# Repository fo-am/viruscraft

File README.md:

# Viruscraft

In this project we ask - what determines the ability of a virus to infect some hosts but not others? Working with evolutionary biologist Ben Longdon, we're developing a citizen science project using visual programming, craft, tangible interfaces and games to explore virus host shifts – where a virus jumps from one host species to another.

https://fo.am/viruscraft/

# todo

- add host extinct/virus extinct to score record
- add virus description to score record
- increase death rate with susceptibility? highly specialised = quicker extinction

aims

-

# Parameters 

These are ones that can be tweaked & need to be checked:

## host-susceptibility

Currently a probability curve between 0 (totally immune) and 1 (certain to get infection)

"returns the susceptibility of the host of infection to the supplied virus
susceptibility will range from 0..1 with 0 being completely immune
pow give us a slope so that 1 is always 1 but we reduce the likelyhood
with fewer receptors - not science"

The point here is to make the successful strategy one of continual
mutation.  In order for this to work, we need to construct a tradeoff
so that viruses with one or two of each type of ligands are not very
good. Specialist viruses should generally be successful to infect.

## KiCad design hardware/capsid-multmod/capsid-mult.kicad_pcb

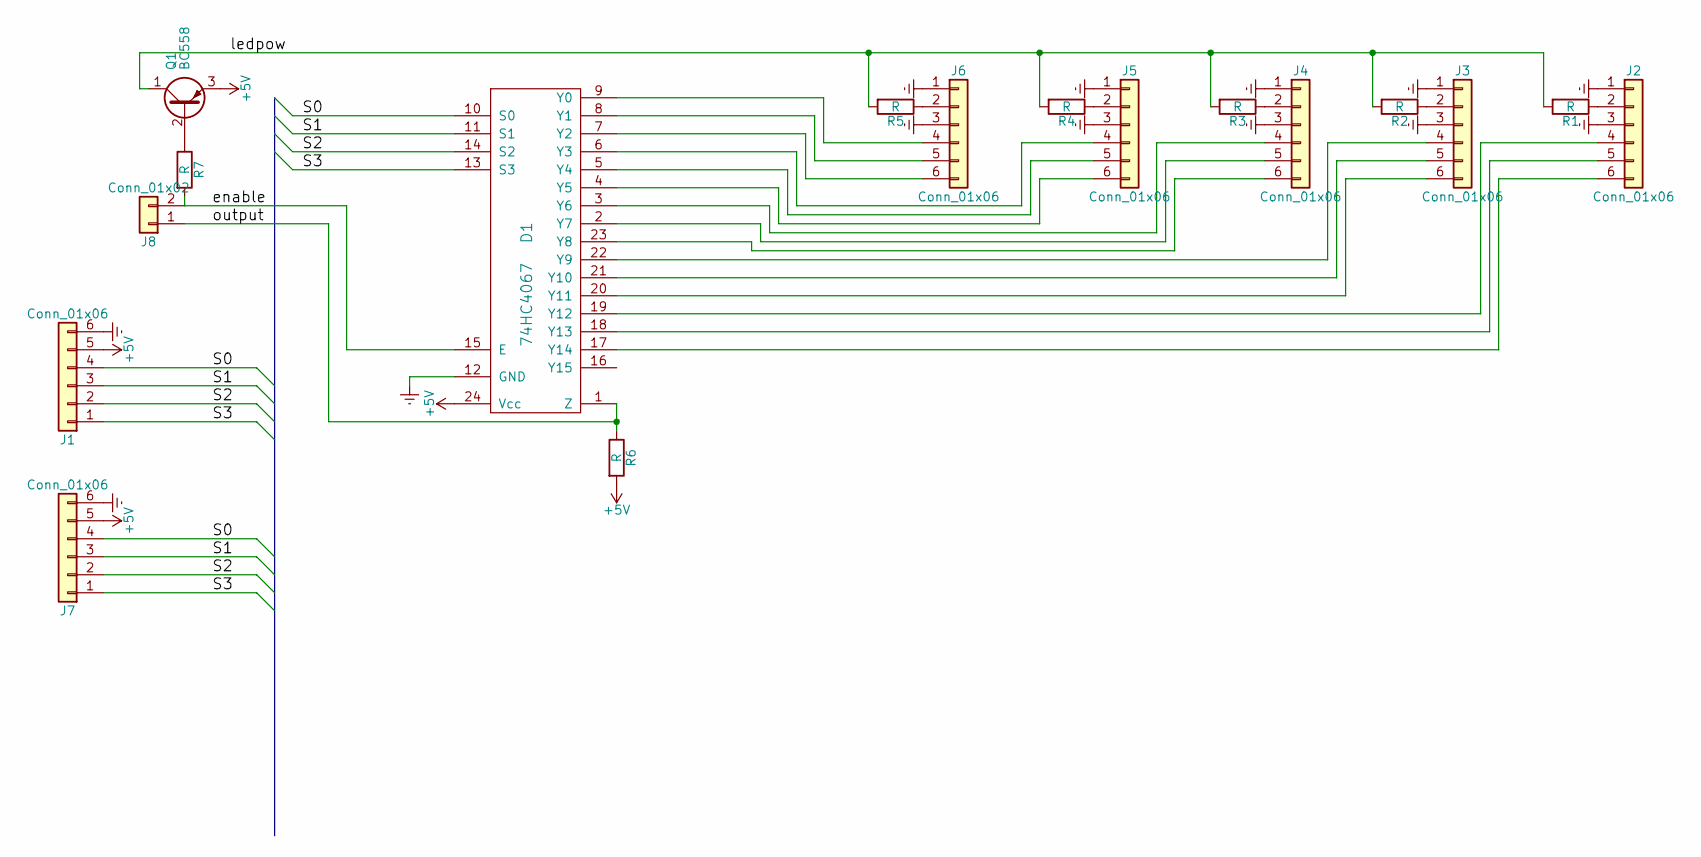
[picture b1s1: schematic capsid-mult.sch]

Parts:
D1: 74HC4067; DIP-24_W15.24mm_Socket
J1, J2, J3, J4, J5, J6, J7: Conn_01x06; Pin_Header_Straight_1x06_Pitch2.54mm
J8: Conn_01x02; Pin_Header_Straight_1x02_Pitch2.54mm
Q1: BC558; TO-92_Inline_Wide
R1, R2, R3, R4, R5, R6, R7: R; R_Axial_DIN0207_L6.3mm_D2.5mm_P10.16mm_Horizontal

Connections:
+5V: D1.24 (Vcc), J1.5, J7.5, Q1.3 (E), R6.2
/S0: D1.10 (S0), J1.4, J7.4
/S1: D1.11 (S1), J1.3, J7.3
/S2: D1.14 (S2), J1.2, J7.2
/S3: D1.13 (S3), J1.1, J7.1
/enable: D1.15 (E), J8.2, R7.2
/ledpow: Q1.1 (C), R1.2, R2.2, R3.2, R4.2, R5.2
/output: D1.1 (Z), J8.1, R6.1
Earth: D1.12 (GND), J1.6, J2.1, J2.3, J3.1, J3.3, J4.1, J4.3, J5.1, J5.3, J6.1, J6.3, J7.6
unnamed: D1.2 (Y7), J4.5
unnamed: D1.3 (Y6), J4.4
unnamed: D1.4 (Y5), J5.6
unnamed: D1.5 (Y4), J5.5
unnamed: D1.6 (Y3), J5.4
unnamed: D1.7 (Y2), J6.6
unnamed: D1.8 (Y1), J6.5
unnamed: D1.9 (Y0), J6.4
unnamed: D1.17 (Y14), J2.6
unnamed: D1.18 (Y13), J2.5
unnamed: D1.19 (Y12), J2.4
unnamed: D1.20 (Y11), J3.6
unnamed: D1.21 (Y10), J3.5
unnamed: D1.22 (Y9), J3.4
unnamed: D1.23 (Y8), J4.6
unnamed: J2.2, R1.1
unnamed: J3.2, R2.1
unnamed: J4.2, R3.1
unnamed: J5.2, R4.1
unnamed: J6.2, R5.1
unnamed: Q1.2 (B), R7.1

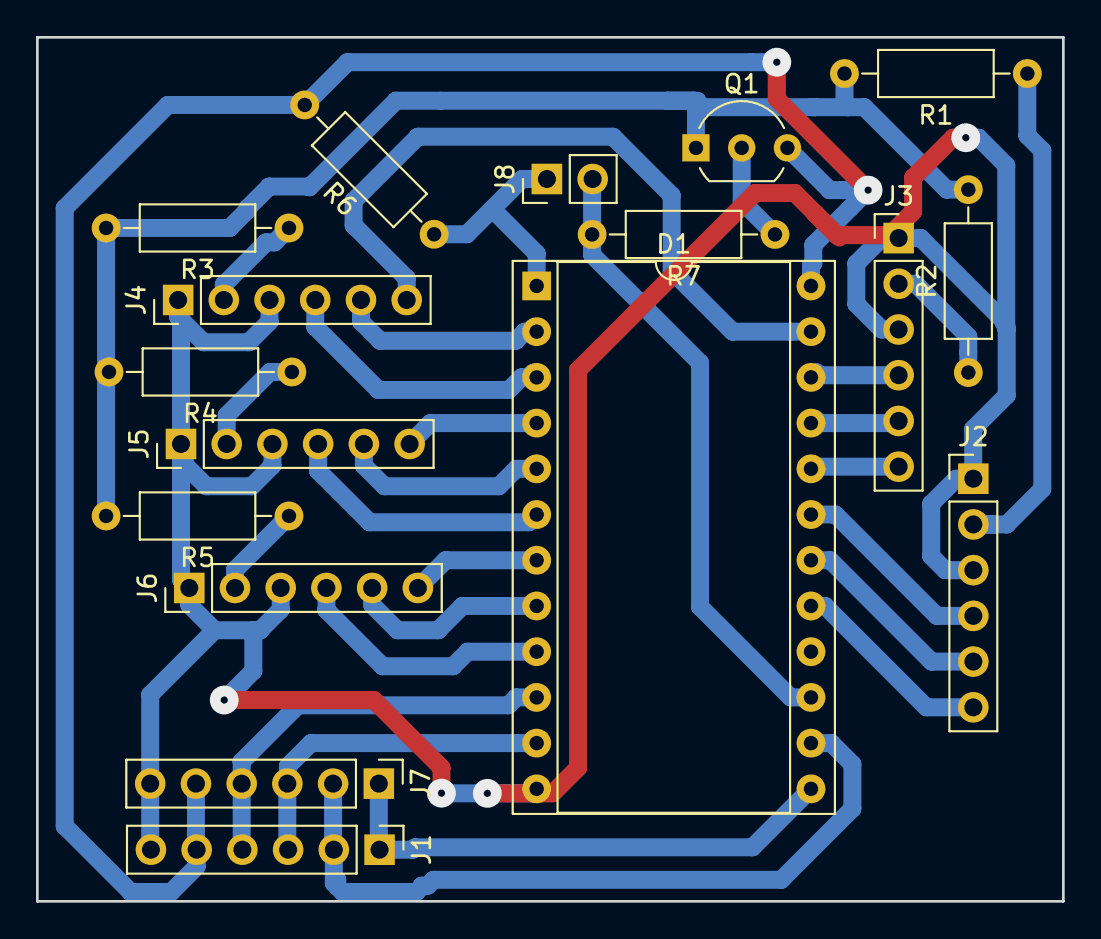
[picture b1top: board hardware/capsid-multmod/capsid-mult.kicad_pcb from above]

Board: 2 copper layers, 57.0 x 48.0 mm, 17 parts (0 on the bottom side), 30 nets.

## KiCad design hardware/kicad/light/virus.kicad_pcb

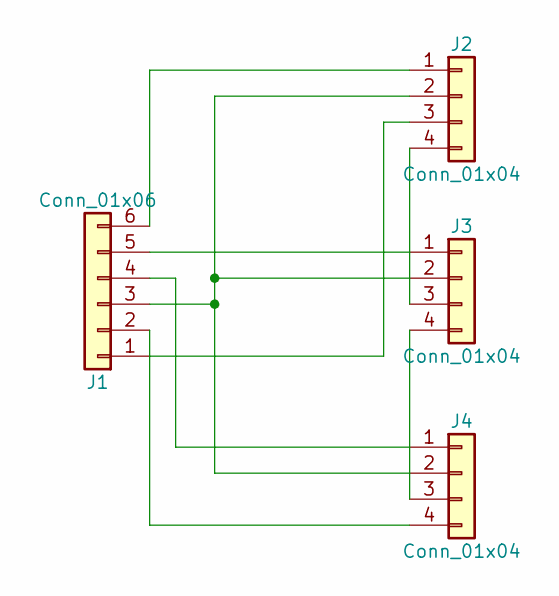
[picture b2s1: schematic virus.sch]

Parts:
J1: Conn_01x06; Pin_Header_Straight_1x06_Pitch2.54mm_SMD_Pin1Right
J2, J3, J4: Conn_01x04; TCRT1000

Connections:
unnamed: J1.1, J2.3
unnamed: J1.2, J4.4
unnamed: J1.3, J2.2, J3.2, J4.2
unnamed: J1.4, J4.1
unnamed: J1.5, J3.1
unnamed: J1.6, J2.1
unnamed: J2.4, J3.3
unnamed: J3.4, J4.3

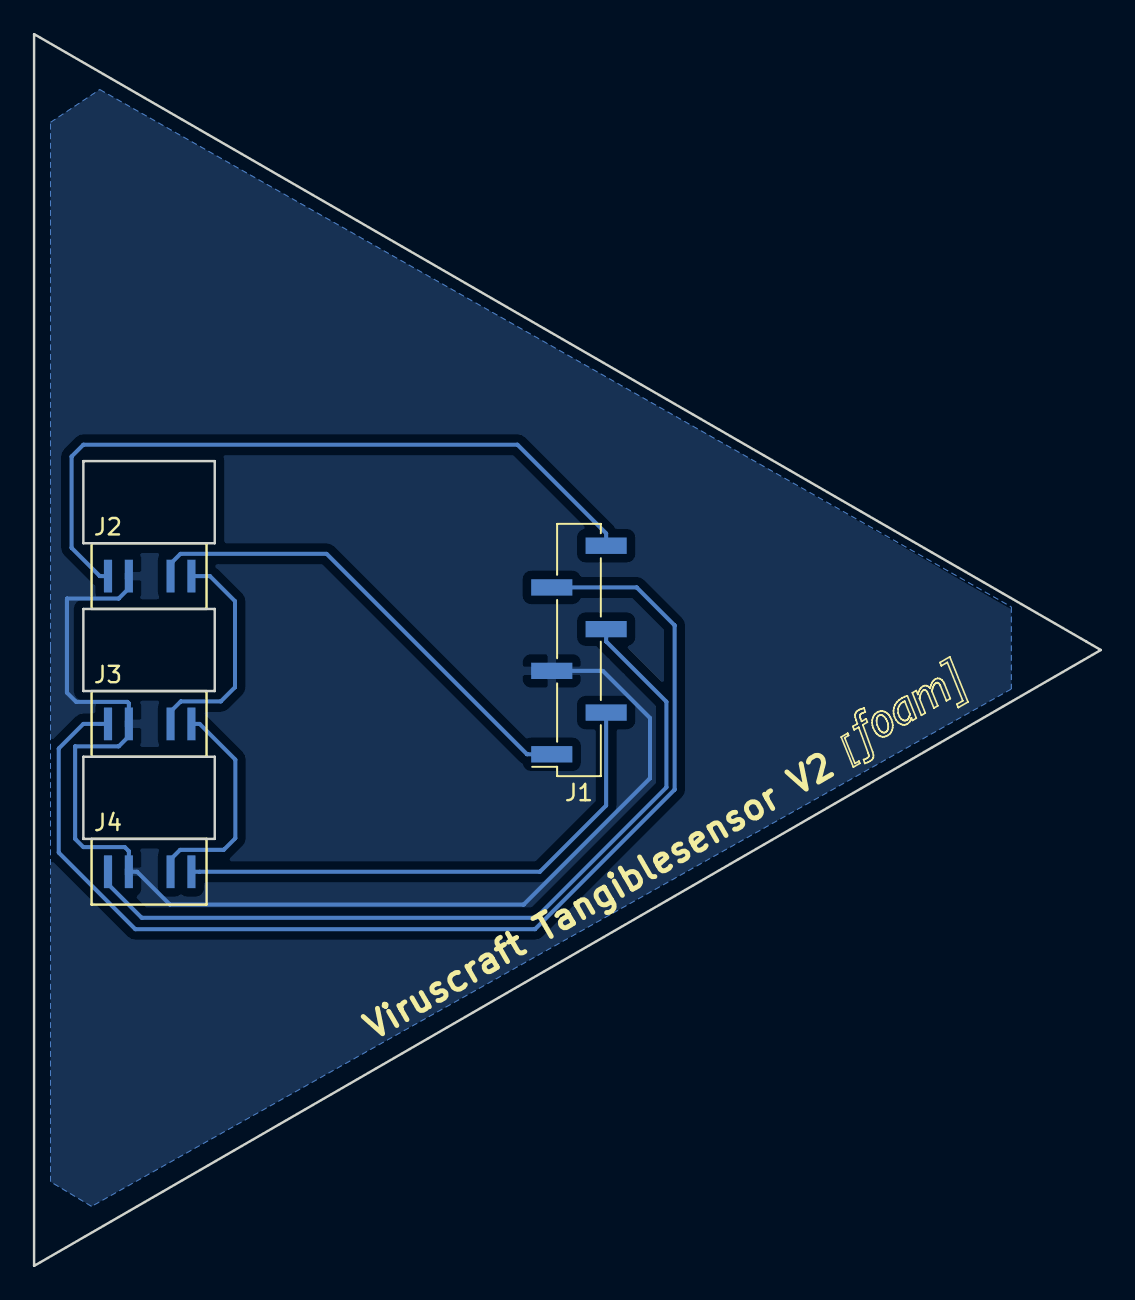
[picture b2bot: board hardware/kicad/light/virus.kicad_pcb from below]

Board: 2 copper layers, 65.0 x 75.0 mm, 4 parts (4 on the bottom side), 8 nets.

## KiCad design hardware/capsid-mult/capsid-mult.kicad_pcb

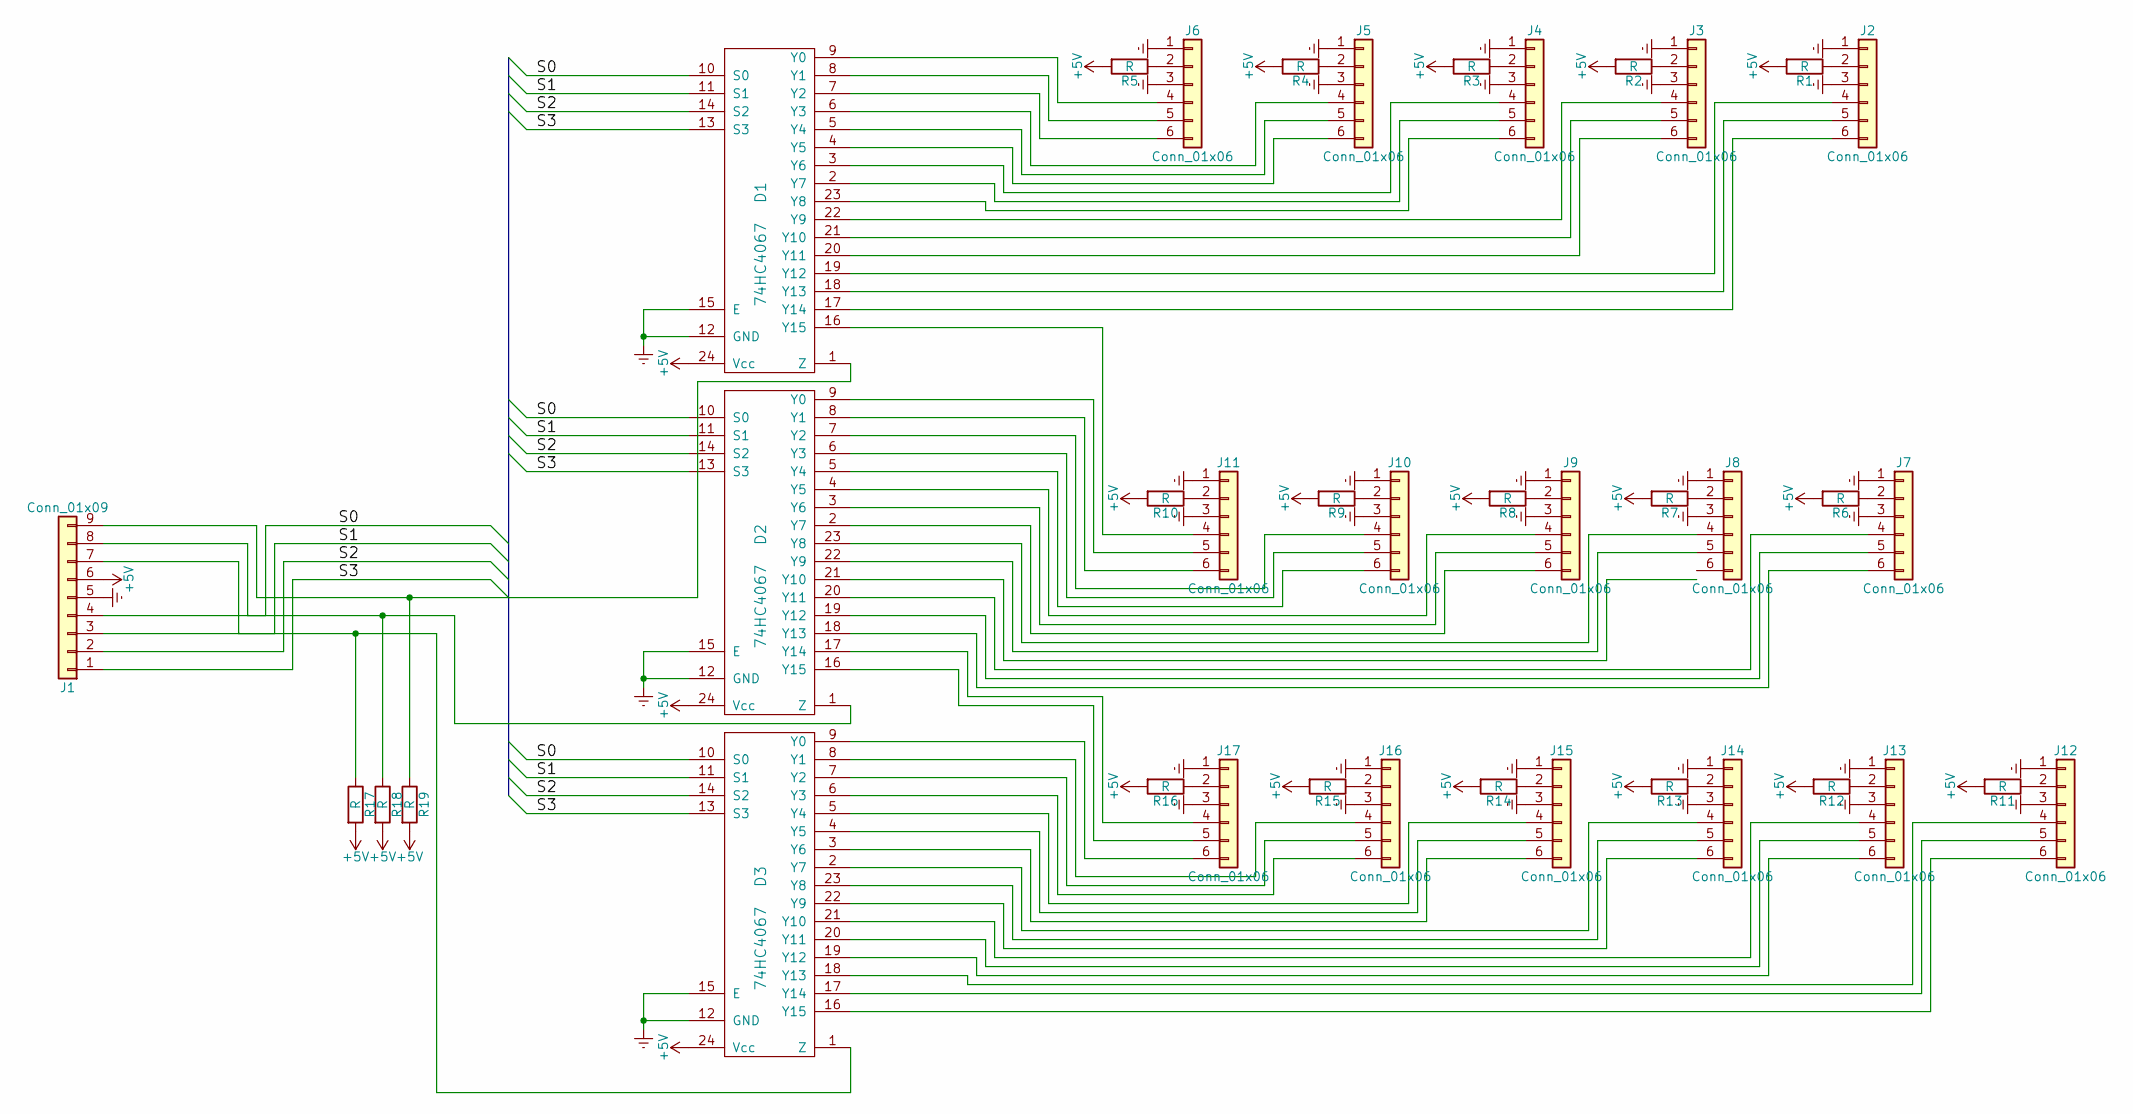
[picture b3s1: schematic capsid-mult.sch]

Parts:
D1, D2, D3: 74HC4067; DIP-24_W15.24mm_Socket
J1: Conn_01x09; Pin_Header_Straight_1x09_Pitch2.54mm
J2, J3, J4, J5, J6, J7, J8, J9, J10, J11, J12, J13, J14, J15, J16, J17: Conn_01x06; Pin_Header_Straight_1x06_Pitch2.54mm
R1, R2, R3, R4, R5, R6, R7, R8, R9, R10, R11, R12, R13, R14, R15, R16, R17, R18, R19: R; R_Axial_DIN0207_L6.3mm_D2.5mm_P10.16mm_Horizontal

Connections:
+5V: D1.24 (Vcc), D2.24 (Vcc), D3.24 (Vcc), J1.6, R1.2, R2.2, R3.2, R4.2, R5.2, R6.2, R7.2, R8.2, R9.2, R10.2, R11.2, R12.2, R13.2, R14.2, R15.2, R16.2, R17.2, R18.2, R19.2
/S0: D1.10 (S0), D2.10 (S0), D3.10 (S0), J1.4
/S1: D1.11 (S1), D2.11 (S1), D3.11 (S1), J1.3
/S2: D1.14 (S2), D2.14 (S2), D3.14 (S2), J1.2
/S3: D1.13 (S3), D2.13 (S3), D3.13 (S3), J1.1
Earth: D1.12 (GND), D1.15 (E), D2.12 (GND), D2.15 (E), D3.12 (GND), D3.15 (E), J1.5, J2.1, J2.3, J3.1, J3.3, J4.1, J4.3, J5.1, J5.3, J6.1, J6.3, J7.1, J7.3, J8.1, J8.3, J9.1, J9.3, J10.1, J10.3, J11.1, J11.3, J12.1, J12.3, J13.1, J13.3, J14.1, J14.3, J15.1, J15.3, J16.1, J16.3, J17.1, J17.3
unnamed: D1.1 (Z), J1.9, R19.1
unnamed: D1.2 (Y7), J4.5
unnamed: D1.3 (Y6), J4.4
unnamed: D1.4 (Y5), J5.6
unnamed: D1.5 (Y4), J5.5
unnamed: D1.6 (Y3), J5.4
unnamed: D1.7 (Y2), J6.6
unnamed: D1.8 (Y1), J6.5
unnamed: D1.9 (Y0), J6.4
unnamed: D1.16 (Y15), J11.4
unnamed: D1.17 (Y14), J2.6
unnamed: D1.18 (Y13), J2.5
unnamed: D1.19 (Y12), J2.4
unnamed: D1.20 (Y11), J3.6
unnamed: D1.21 (Y10), J3.5
unnamed: D1.22 (Y9), J3.4
unnamed: D1.23 (Y8), J4.6
unnamed: D2.1 (Z), J1.8, R18.1
unnamed: D2.2 (Y7), J9.6
unnamed: D2.3 (Y6), J9.5
unnamed: D2.4 (Y5), J9.4
unnamed: D2.5 (Y4), J10.6
unnamed: D2.6 (Y3), J10.5
unnamed: D2.7 (Y2), J10.4
unnamed: D2.8 (Y1), J11.6
unnamed: D2.9 (Y0), J11.5
unnamed: D2.16 (Y15), J17.5
unnamed: D2.17 (Y14), J17.4
unnamed: D2.18 (Y13), J7.6
unnamed: D2.19 (Y12), J7.5
unnamed: D2.20 (Y11), J7.4
unnamed: D2.22 (Y9), J8.5
unnamed: D2.23 (Y8), J8.4
unnamed: D3.1 (Z), J1.7, R17.1
unnamed: D3.2 (Y7), J14.4
unnamed: D3.3 (Y6), J15.6
unnamed: D3.4 (Y5), J15.5
unnamed: D3.5 (Y4), J15.4
unnamed: D3.6 (Y3), J16.6
unnamed: D3.7 (Y2), J16.5
unnamed: D3.8 (Y1), J16.4
unnamed: D3.9 (Y0), J17.6
unnamed: D3.16 (Y15), J12.6
unnamed: D3.17 (Y14), J12.5
unnamed: D3.18 (Y13), J12.4
unnamed: D3.19 (Y12), J13.6
unnamed: D3.20 (Y11), J13.5
unnamed: D3.21 (Y10), J13.4
unnamed: D3.22 (Y9), J14.6
unnamed: D3.23 (Y8), J14.5
unnamed: J2.2, R1.1
unnamed: J3.2, R2.1
unnamed: J4.2, R3.1
unnamed: J5.2, R4.1
unnamed: J6.2, R5.1
unnamed: J7.2, R6.1
unnamed: J8.2, R7.1
unnamed: J9.2, R8.1
unnamed: J10.2, R9.1
unnamed: J11.2, R10.1
unnamed: J12.2, R11.1
unnamed: J13.2, R12.1
unnamed: J14.2, R13.1
unnamed: J15.2, R14.1
unnamed: J16.2, R15.1
unnamed: J17.2, R16.1

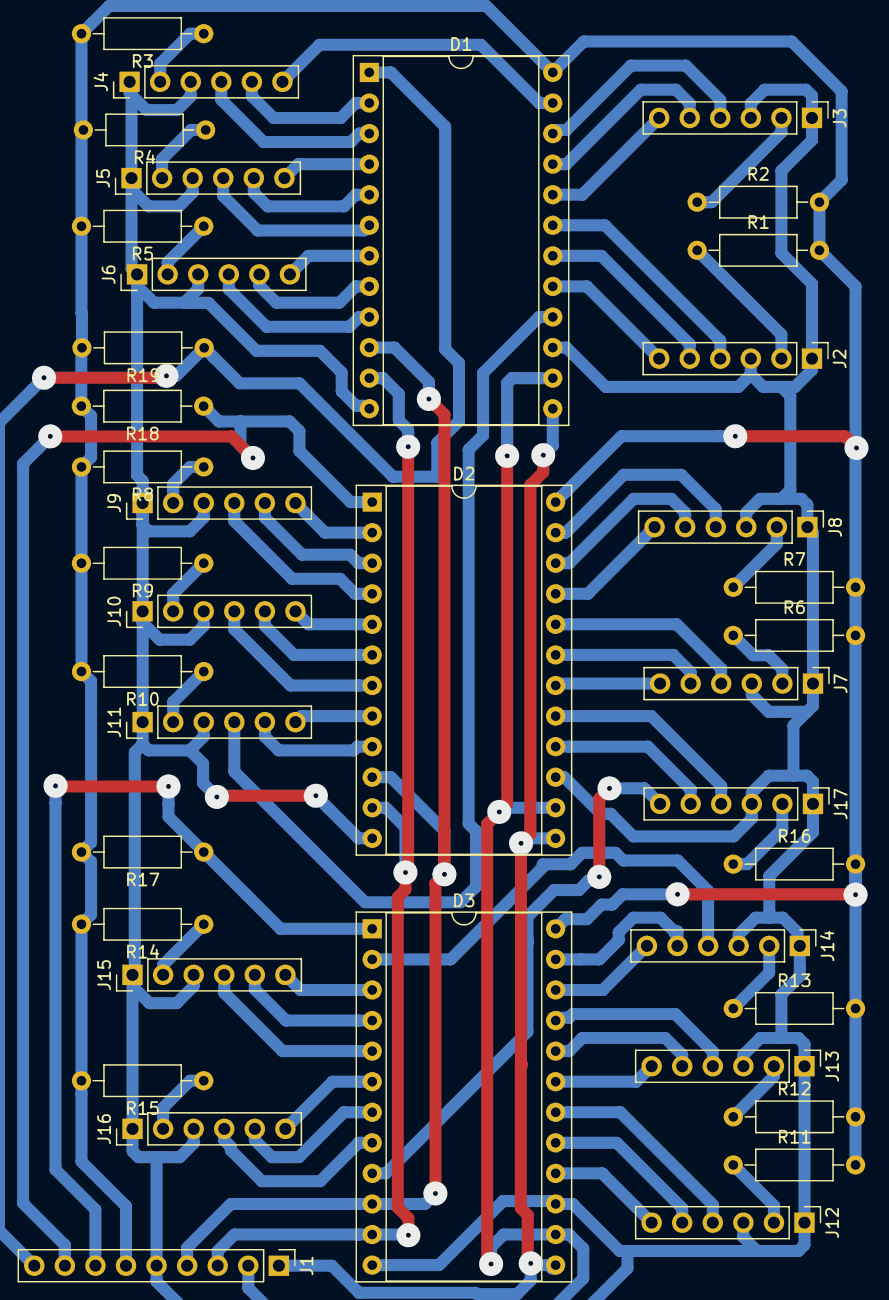
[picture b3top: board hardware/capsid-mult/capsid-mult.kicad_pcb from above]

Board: 2 copper layers, 39 parts (0 on the bottom side), 72 nets.

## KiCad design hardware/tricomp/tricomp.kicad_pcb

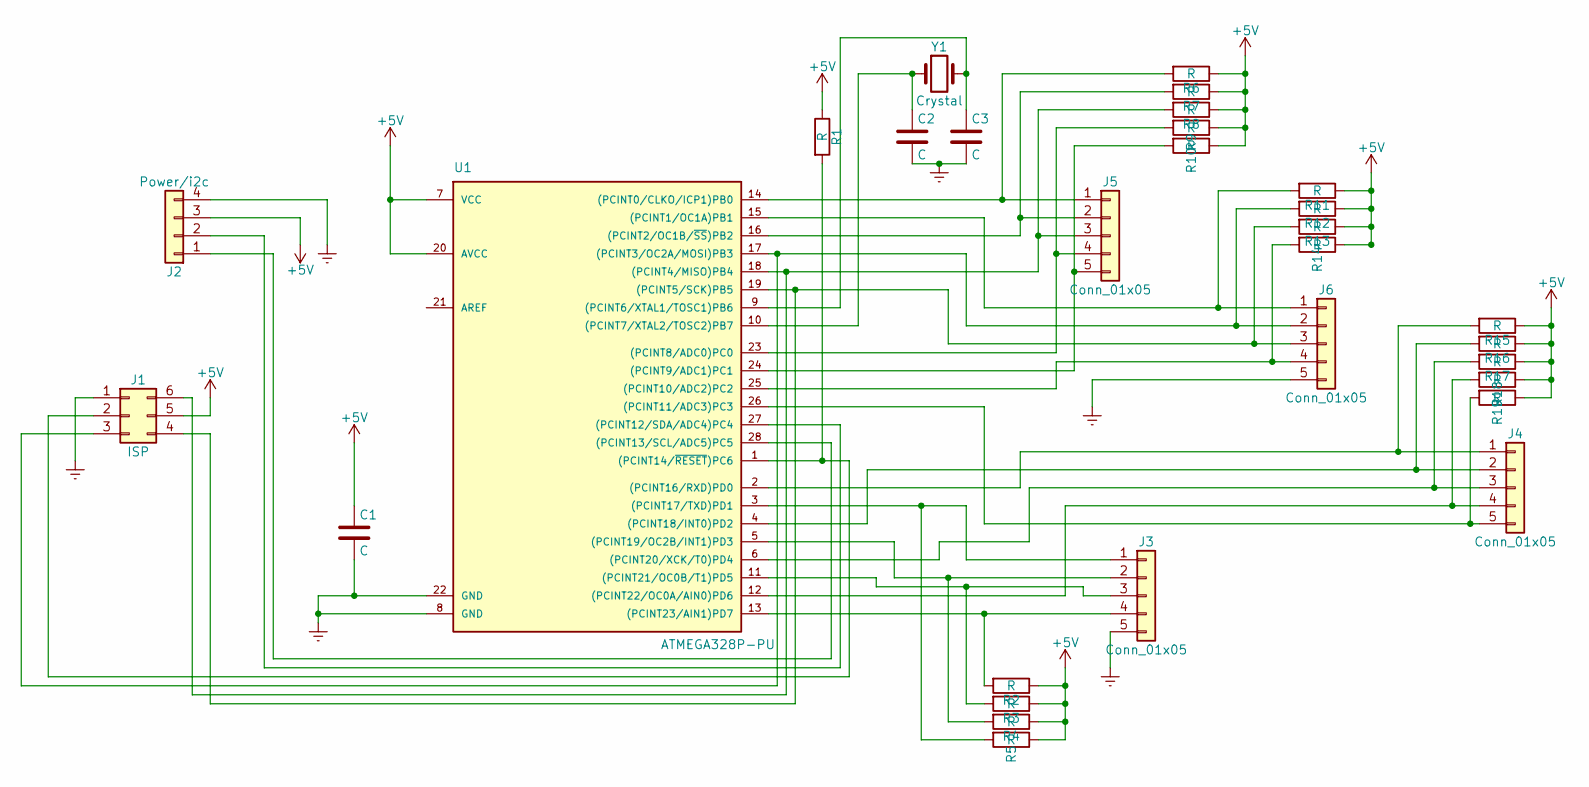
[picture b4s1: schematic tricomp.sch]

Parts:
C1, C2, C3: C; C_Axial_L3.8mm_D2.6mm_P7.50mm_Horizontal
J1: ISP; Pin_Header_Straight_2x03_Pitch2.54mm
J2: Power/i2c; Pin_Header_Straight_1x04_Pitch2.54mm
J3, J4, J5, J6: Conn_01x05; Pin_Header_Straight_1x05_Pitch2.54mm
R1, R2, R3, R4, R5, R6, R7, R8, R9, R10, R11, R12, R13, R14, R15, R16, R17, R18, R19: R; R_Axial_DIN0204_L3.6mm_D1.6mm_P7.62mm_Horizontal
U1: ATMEGA328P-PU; DIP-28_W7.62mm
Y1: Crystal; TerminalBlock_bornier-2_P5.08mm

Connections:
+5V: C1.1, J1.5, J2.3, R1.1, R2.1, R3.1, R4.1, R5.1, R6.1, R7.1, R8.1, R9.1, R10.1, R11.1, R12.1, R13.1, R14.1, R15.1, R16.1, R17.1, R18.1, R19.1, U1.7 (VCC), U1.20 (AVCC)
Earth: C1.2, C2.2, C3.2, J1.1, J2.4, J3.5, J6.5, U1.8 (GND), U1.22 (GND)
unnamed: C2.1, U1.10 ((PCINT7/XTAL2/TOSC2)PB7), Y1.1
unnamed: C3.1, U1.9 ((PCINT6/XTAL1/TOSC1)PB6), Y1.2
unnamed: J1.2, R1.2, U1.1 ((PCINT14/~RESET~)PC6)
unnamed: J1.3, J6.2, R12.2, U1.17 ((PCINT3/OC2A/MOSI)PB3)
unnamed: J1.4, J6.3, R13.2, U1.19 ((PCINT5/SCK)PB5)
unnamed: J1.6, J5.3, R8.2, U1.18 ((PCINT4/MISO)PB4)
unnamed: J2.1, U1.28 ((PCINT13/SCL/ADC5)PC5)
unnamed: J2.2, U1.27 ((PCINT12/SDA/ADC4)PC4)
unnamed: J3.1, R5.2, U1.3 ((PCINT17/TXD)PD1)
unnamed: J3.2, R4.2, U1.5 ((PCINT19/OC2B/INT1)PD3)
unnamed: J3.3, R3.2, U1.11 ((PCINT21/OC0B/T1)PD5)
unnamed: J3.4, R2.2, U1.13 ((PCINT23/AIN1)PD7)
unnamed: J4.1, R15.2, U1.2 ((PCINT16/RXD)PD0)
unnamed: J4.2, R16.2, U1.4 ((PCINT18/INT0)PD2)
unnamed: J4.3, R17.2, U1.6 ((PCINT20/XCK/T0)PD4)
unnamed: J4.4, R18.2, U1.12 ((PCINT22/OC0A/AIN0)PD6)
unnamed: J4.5, R19.2, U1.26 ((PCINT11/ADC3)PC3)
unnamed: J5.1, R6.2, U1.14 ((PCINT0/CLKO/ICP1)PB0)
unnamed: J5.2, R7.2, U1.16 ((PCINT2/OC1B/~SS~)PB2)
unnamed: J5.4, R9.2, U1.23 ((PCINT8/ADC0)PC0)
unnamed: J5.5, R10.2, U1.24 ((PCINT9/ADC1)PC1)
unnamed: J6.1, R11.2, U1.15 ((PCINT1/OC1A)PB1)
unnamed: J6.4, R14.2, U1.25 ((PCINT10/ADC2)PC2)

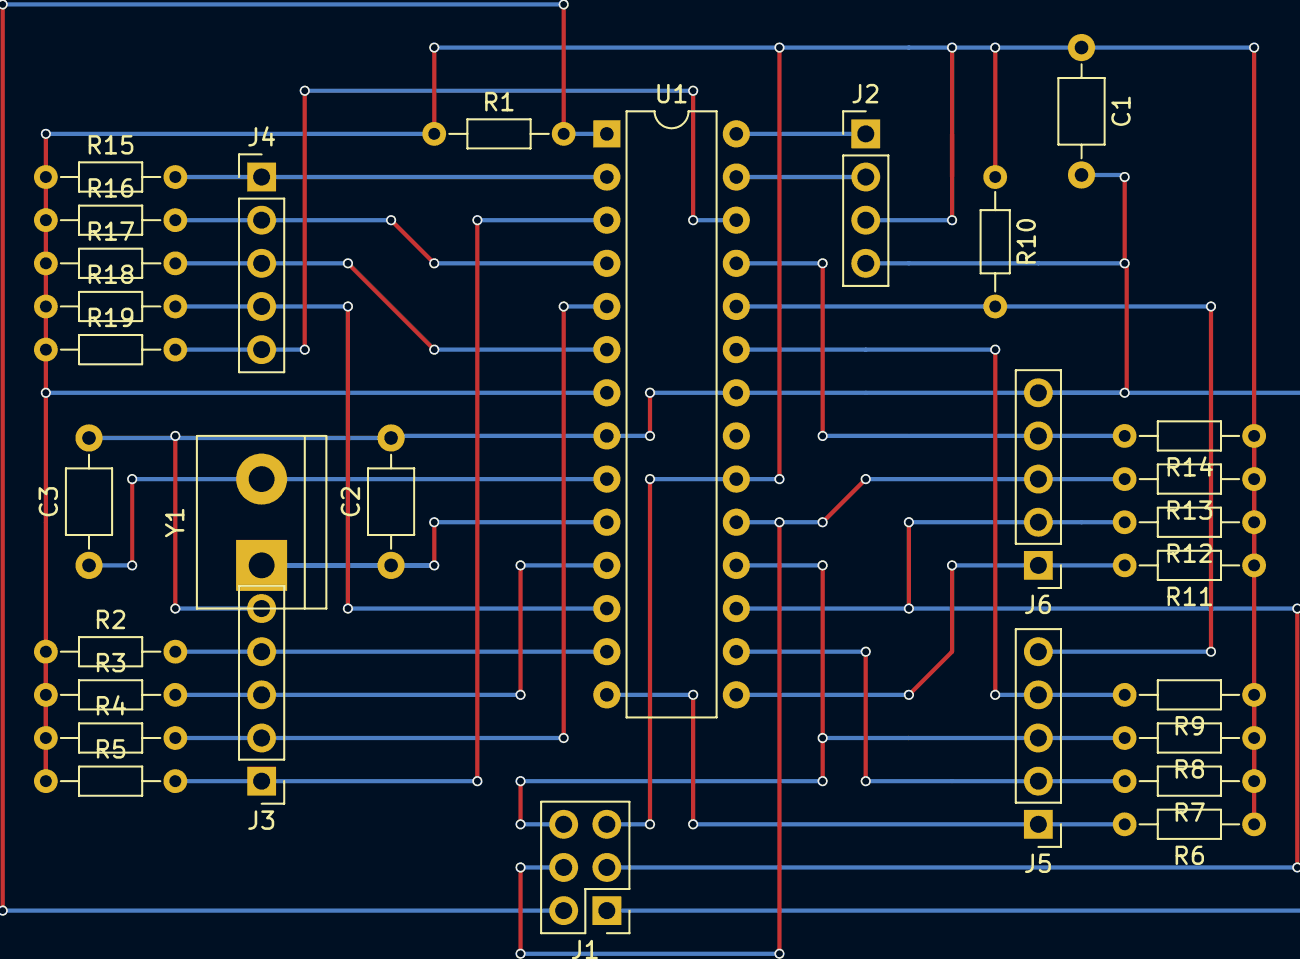
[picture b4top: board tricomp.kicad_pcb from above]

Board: 2 copper layers, 30 parts (0 on the bottom side), 25 nets.

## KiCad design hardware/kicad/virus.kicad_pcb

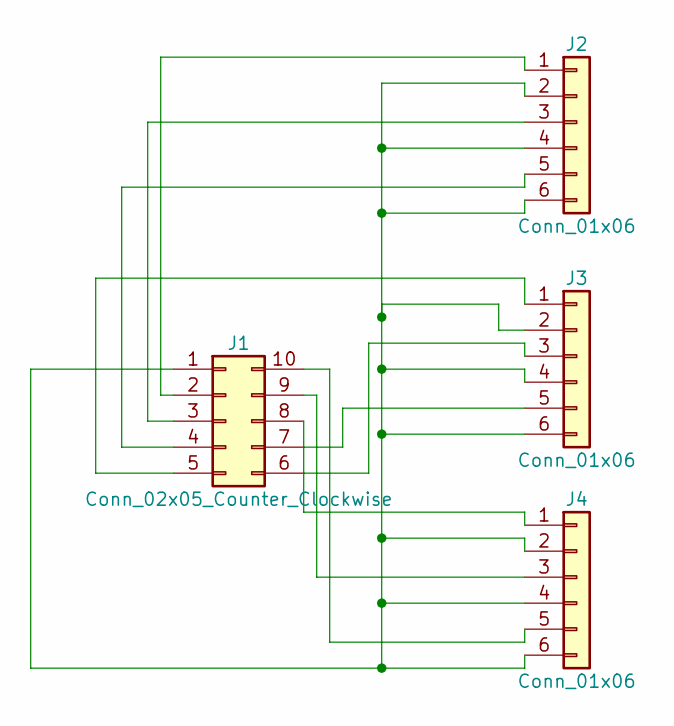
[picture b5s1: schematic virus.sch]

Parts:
J1: Conn_02x05_Counter_Clockwise; Pin_Header_Straight_1x10_Pitch2.00mm_SMD_Pin1Left
J2, J3, J4: Conn_01x06; detector_pad_6

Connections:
unnamed: J1.1, J2.2, J2.4, J2.6, J3.2, J3.4, J3.6, J4.2, J4.4, J4.6
unnamed: J1.2, J2.1
unnamed: J1.3, J2.3
unnamed: J1.4, J2.5
unnamed: J1.5, J3.1
unnamed: J1.6, J3.3
unnamed: J1.7, J3.5
unnamed: J1.8, J4.1
unnamed: J1.9, J4.3
unnamed: J1.10, J4.5

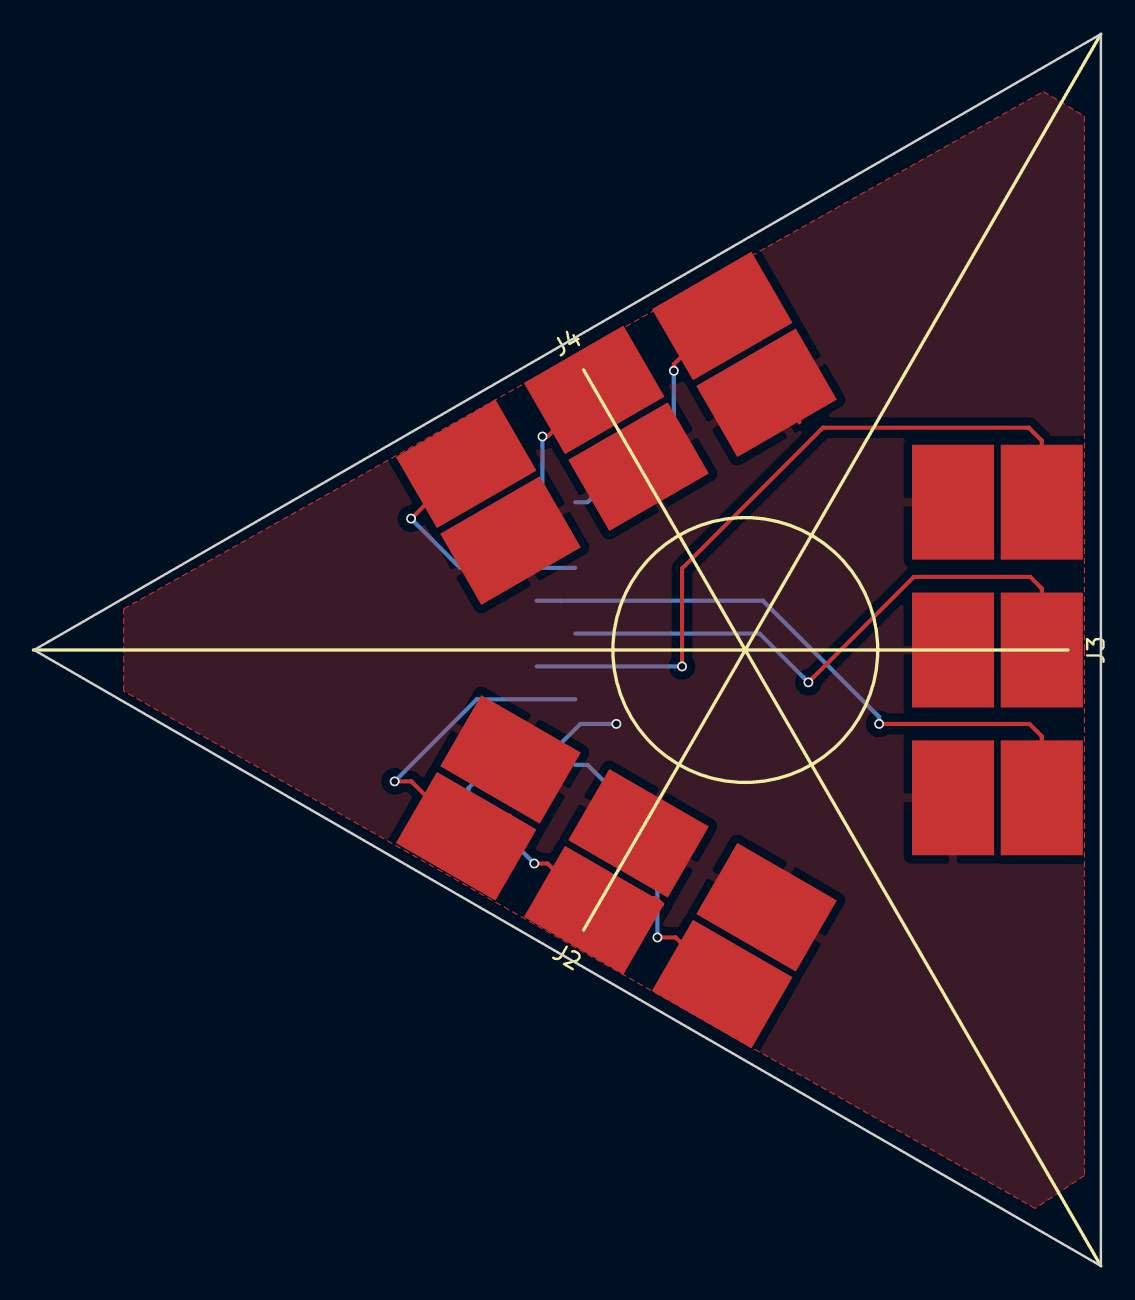
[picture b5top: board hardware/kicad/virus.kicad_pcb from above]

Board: 2 copper layers, 65.0 x 75.0 mm, 4 parts (1 on the bottom side), 10 nets.

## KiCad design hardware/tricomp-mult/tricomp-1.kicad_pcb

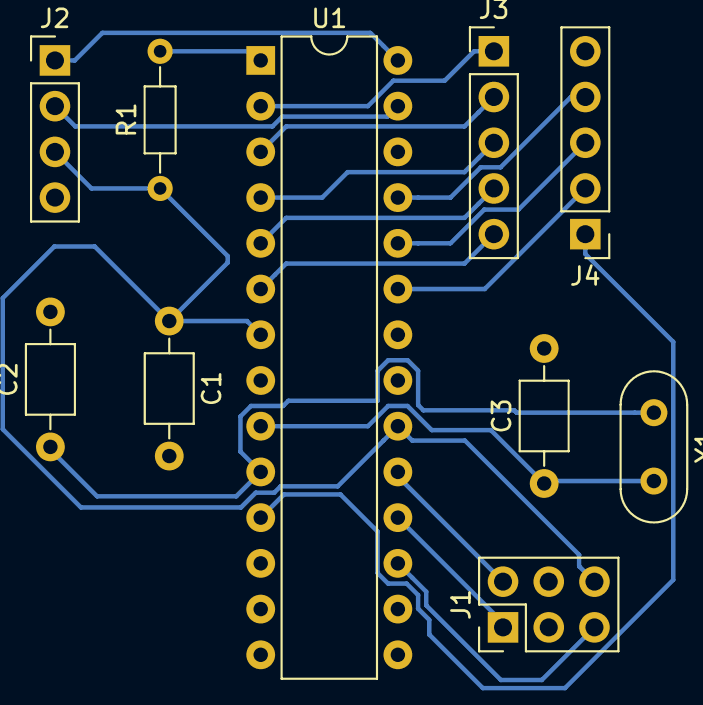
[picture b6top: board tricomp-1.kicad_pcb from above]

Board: 2 copper layers, 10 parts (0 on the bottom side), 19 nets.

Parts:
C1, C2, C3: C; C_Axial_L3.8mm_D2.6mm_P7.50mm_Horizontal
J1: ISP; Pin_Header_Straight_2x03_Pitch2.54mm
J2: Power/i2c; Pin_Header_Straight_1x04_Pitch2.54mm
J3, J4: Conn_01x05; Pin_Header_Straight_1x05_Pitch2.54mm
R1: R; R_Axial_DIN0204_L3.6mm_D1.6mm_P7.62mm_Horizontal
U1: ATMEGA328P-PU; DIP-28_W7.62mm
Y1: Crystal; Crystal_HC52-8mm_Vertical

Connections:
+5V: C1.1, J1.6, J2.3, R1.1, U1.7, U1.20
Earth: C1.2, C2.2, C3.2, J1.4, J2.4, J4.5, U1.8, U1.22
unnamed: C2.1, U1.10, Y1.1
unnamed: C3.1, U1.9, Y1.2
unnamed: J1.1, U1.18
unnamed: J1.2, U1.19
unnamed: J1.3, R1.2, U1.1
unnamed: J1.5, U1.17
unnamed: J2.1, U1.28
unnamed: J2.2, U1.27
unnamed: J3.1, U1.2
unnamed: J3.2, U1.3
unnamed: J3.3, U1.4
unnamed: J3.4, U1.5
unnamed: J3.5, U1.6
unnamed: J4.1, U1.11
unnamed: J4.2, U1.23
unnamed: J4.3, U1.24
unnamed: J4.4, U1.25

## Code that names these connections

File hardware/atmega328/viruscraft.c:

#define F_CPU F_OSC

#include <avr/io.h>
#include <util/delay.h>
#include <stdlib.h>
#include <avr/interrupt.h>
#include <avr/wdt.h>
#include "I2C_slave.h"

//#define SINGLE_SENSOR
#define I2C_ID 0x32

#define STATUS_PORT_D DDRC
#define STATUS_PORT PORTC
#define PIN_STATUS PC3

unsigned char receptor_donut    = 0x0; // 000
unsigned char receptor_triangle = 0x1; // 001
unsigned char receptor_circle   = 0x2; // 010
unsigned char receptor_square   = 0x3; // 011
unsigned char receptor_angle    = 0x4; // 100
unsigned char receptor_guitar   = 0x5; // 101
unsigned char receptor_tee      = 0x6; // 110
unsigned char receptor_none     = 99;

unsigned char num_receptors=7;

unsigned char thresh[] = {1,2,2,2,2,2,2,99};

unsigned char filter_receptors(unsigned char a, unsigned char b, unsigned char c) {
  if (a==b==c) return a;
  if (thresh[a]<=1) return a;
  if (thresh[b]<=1) return b;
  if (thresh[c]<=1) return c;
  if ((a==b || a==c) && thresh[a]<=2) return a;
  if ((b==a || b==c) && thresh[b]<=2) return b;
  return receptor_none;
}

// address registers
//            PB1 PB3 PB5 PC2
//         00 01 02 03 04 05 06 07
// PORT B: xx AA xx BB xx CC xx xx
// PORT C: xx xx DD xx xx xx xx xx

void set_addr(unsigned char addr) {
  PORTB = (addr&0x01)<<1 |
          (addr&0x02)<<2 |
          (addr&0x04)<<2;
  PORTC = (addr&0x08)>>1;
}

// receptor registers

//          00 01 02 03 04 05 06 07
// Port D: |A1 A2 A3|B3 B2 B1|C1 C2| 
// Port C:  xx xx xx|C3|xx xx xx xx

unsigned char read_a() {
  return PIND&0x07;
}

unsigned char read_b() {
  // flipped, sigh...
  return (PIND&0x20)>>5 |
         (PIND&0x10)>>3 |
         (PIND&0x08)>>1;
}

unsigned char read_c() {
  return ((PIND&0xC0)>>6) | ((PINC&0x08)>>1);
}

void set_led_state(unsigned char s) {
    if (s) STATUS_PORT|=_BV(PIN_STATUS);
    else STATUS_PORT&=~_BV(PIN_STATUS);
}

////////////////////////////////////////////////////////

int main(void) {
  I2C_init(I2C_ID<<1); // initalize as slave with address 0x32
  
  sei();
  //   MCUSR = 0;
  //wdt_disable();
  
  DDRC = 0x04;
  DDRD = 0x00; // input
  DDRB = 0xff; // output

  for (int i=0; i<0xFF; i++) {
    i2cbuffer[i]=99;
  }

  unsigned char led=0;

  //  PORTC|=_BV(FACE_SELECT_PIN);
  //PORTC&=~_BV(FACE_SELECT_PIN);

  unsigned int count=0;

  while(1) {    
    i2cbuffer[0]=count;
    count++;

    unsigned int bufferpos=1;
    for (unsigned char addr=0; addr<3; addr++) {
      //set_addr(addr);

      switch(addr) {
      case 0: 
	PORTB&=~_BV(PB1);
	PORTB&=~_BV(PB3);
	break;
      case 1:
	PORTB|=_BV(PB1); 
	PORTB&=~_BV(PB3);
	break;
      case 2:
	PORTB&=~_BV(PB1);
	PORTB|=_BV(PB3); 
	break;
      }

      _delay_ms(250);

      //i2cbuffer[bufferpos++]=read_a();
      //i2cbuffer[bufferpos++]=read_b();
      //i2cbuffer[bufferpos++]=read_c();

      i2cbuffer[bufferpos++]=
      	filter_receptors(read_a(),read_b(),read_c());

      _delay_ms(250);
    }

    //    _delay_ms(500);
    //set_led_state(1);
    //_delay_ms(20);
    //set_led_state(0);
    //    wdt_reset();
  }
}

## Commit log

2017-02-20 added image to readme
2017-03-03 added world
2017-04-11 added web experiments
2017-04-11 started new prototype and tidy up
2017-04-12 new prototype
2017-04-12 connections for plants on second prototype
2017-04-13 tidy and presentation
2017-04-13 words
2017-04-13 text
2017-04-13 font changes
2017-04-15 massive optimisations, primitive types
2017-04-18 interleaved vbo support, pdata-map, refactor...
2017-04-20 livecoding
2017-04-21 added capsid protein structure prototype
2017-04-21 main page capsid link added
2017-04-21 added capsid button
2017-04-28 lsystem tweaks and stuff for workshop
2017-06-14 some experimenting...
2017-06-20 added genetic experiment
2017-07-18 fixed build-polygons for procedural modelling
2017-07-18 extruder, without proper normal gen yet
2017-07-18 smoothed extrude
2017-07-18 update with new prototype
2017-07-18 added extrude files
2017-07-19 bendy phyloextrusions
2017-07-19 got model running with tree viz
2017-07-19 audo restart
2017-07-21 tree viz and model working
2017-07-21 simplified trees
2017-07-23 massive optimisations
2017-07-31 added first world proto
2017-07-31 text fix
2017-07-31 image tweak
2017-07-31 added logo
2017-08-02 planet proto added
2017-08-02 Create wood
2017-08-02 Add files via upload
    Mockups laser cutting shapes for 1 truncated icosidodecahedron and 1 icosohedron
2017-08-02 shader work mostly
2017-08-02 added reduced planet
2017-08-02 clear sold
2017-08-02 black bg on firefox
2017-09-10 new sped up single receptor version
2017-09-13 playable is more playable
2017-09-15 virus builder
2017-09-15 new images
2017-09-15 high scores and feedback on the playable prototype
2017-09-15 added playable proto files
2017-09-18 hid playable
2017-09-18 alpha tweak
2017-09-18 more virulent
2017-09-19 fixed broken div
2017-10-12 balancing crafting prototype
2017-10-12 link fix
2017-11-29 added new model based on single receptor one
2017-11-29 cleanup and returned to rotating planet
2017-12-01 texture coords loading, clouds and things
2017-12-03 investigating the difference between equalaterals and isocelese
2017-12-03 some kind of fix
2017-12-05 fixed orientation...
2018-01-16 unit world working...
2018-01-16 more missing things
2018-01-19 shader regression and site updates
2018-01-31 moved core engine
2018-02-05 started assembiling main game code
2018-02-09 loads of species, animation and models
2018-02-09 removed unused materials
2018-02-11 loads of error checking added to compiler, started work on world placement
2018-02-12 added hide, scenegraph fix and lots of terrain searching added
2018-02-12 towards splitting land and sea creatures
2018-02-13 fixed species placement
2018-02-16 new models mostly
2018-02-16 added geometry
2018-03-20 fullscreen stuff and objects as buttons working - broken prototypes
2018-03-22 dragging virus and world, virus face select started
2018-03-22 perspective tweak, trashed prototypes again
2018-03-26 mainly hardware updates, atmel firmware etc
2018-03-27 world zooming, model tweaks
2018-03-29 added game modes
2018-03-29 fixed virus builder
2018-03-30 meshcache, preloading and pdata-add
2018-03-30 arbitrary pdata - shader attributes
2018-03-31 gpu animation, arbitrary shader parameters working, pdata-set and time fix to be elapsed
2018-03-31 precompiled shaders
2018-03-31 shader tweaks
2018-04-01 more modes
2018-04-02 screen switching and world design mode
2018-04-06 building stripboard prototype
2018-04-10 styyyyyyle
2018-04-10 bg image added
2018-04-10 popups
2018-04-10 popups and colours
2018-04-10 fixes for transitions
2018-04-12 hardware fixes, moving stuff around etc
2018-04-12 host jumps added
2018-04-12 fixed prototypes!
2018-04-12 new shader
2018-04-12 android fixes
2018-04-12 merge
2018-04-14 new receptors, jump highlight test and mem leak fix
2018-04-14 shader unforms fixed for state
2018-04-15 glsl fixes and more gpu animation, infection highlights
2018-04-16 host texture file
2018-04-18 remote receptor changes
2018-04-19 fixed 111 worldunit and added variation, mushrooms, hardware fixes and removed fin on sea creature
2018-04-20 tangibleification
2018-05-06 moved to flx submodule shared with malaria project
2018-05-06 Create LICENSE
2018-08-26 added lots of hardware stuff
2018-12-10 new cnc pcb and new firmware
2018-12-10 lots of missing hardware stuff
2018-12-13 new threshold
2018-12-13 new exhibition mode, rotate to transmission, min host size fixed: #4
2018-12-13 upgraded flx, framerate independance, slowed down time, added end game exit, fixed: #6
2018-12-14 server for high scores, sorting out scoring, starting to document parameters
2018-12-14 added leaderboard in play area, sorted layout and added a stats mode
2018-12-15 built stats screen
2018-12-16 made it fun
2018-12-17 fixed rotation, added mutation recording etc
2018-12-17 rotation fixes and debug stuff turned off
2018-12-17 pi version things
2018-12-17 exhibiton fixes from the pi
2019-01-08 adding stuff from virus pi
2019-01-08 darker hosts fixed: #28 current infections now work fixed: #24
2019-01-08 randomise sea level fixed: #26
2019-01-08 text fixes, difficulty fix etc fixed: #21 fixed: #20
2019-01-08 cache hack for receptors, land creatures fixed: #9
2019-01-09 changed range of random sea level and finally fixed triangle rotation problem fixed: #27
2019-01-09 text tweak and fixed flying hosts fixed: #18
2019-01-09 removed infection highlights on other side of the planet, another flying host fix, fixed: #25
2019-01-09 clean up
2019-01-10 last minute fixes
2019-01-10 added startup sound
2019-02-12 model changes from eden workshop
2019-02-12 added about mode
2019-02-14 organisms moving, mostly
2019-02-14 organisms moving properly, need to bring back spatial constraint to spawning and refactor a bit
2019-02-17 movement working and fixed health bug when infected
2019-02-17 increased difficulty and smoothed host rotation
2019-02-18 fixes for warping and rotation-scaling of hosts
2019-02-18 towards a sensible aspect ratio model
2019-02-21 difficulty tweaks for moving hosts and lots of fixes
2019-02-21 world design new slider and noise generator
2019-02-22 more formatting and new images
2019-02-22 added images
2019-02-22 prototypes page
2019-02-22 loading font fix
2019-02-22 tweaks
2019-02-22 added record virus button and added world params to db fixed: #38 fixed: 37
2019-02-25 started about and sounds
2019-02-25 about pages
2019-02-26 new help system
2019-02-28 help bubble and text box fixes
2019-03-01 more help, text and layout tweaks
2019-03-01 popup pos
2019-03-01 QA fixes
2019-03-01 more QA fixes
2019-04-11 simplified about
2019-04-11 text tweak
2020-04-02 Add files via upload
    Image files for viruscraft stickers
2020-05-17 added vcckit files
2020-05-17 imodela gcode fixes
2020-05-18 added good gcode
2020-05-21 full structure made
2020-06-02 vcckit struct v2 working, building second half
2020-10-06 updated new designs
2020-12-10 sped up camera drift Fixed: #42
2020-12-10 transmission circles now under dialogs Fixed: #41
2020-12-10 added favicon
2020-12-10 new title and fixed info bubble flicker Fixed: #43
2020-12-10 skipping world design mode Fixed: #44
2020-12-10 About text tweak Fixed: #45
2020-12-10 Front page text Fixed: #46
2020-12-10 slowed down movement, increased infection mult
2020-12-10 reduced skipping around the world too much
2020-12-10 added a new help bubble Fixed: #50
2020-12-10 more tweaks
2020-12-10 server fixes
2020-12-11 fixed sticky world problem
2020-12-11 restrict scores to the previous week's viruses
